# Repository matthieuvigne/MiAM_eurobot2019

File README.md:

# MiAM_eurobot2019
## Electronics and code of MiAM's robot for Eurobot 2019.

This repo contains code and electronics design files related the 2019 Eurobot competition of MiAM,
a French team of former students from MINES ParisTech and Arts et Métiers schools.

For older files related to the 2018 robot setup, see [MiAM_eurobot2018](https://github.com/matthieuvigne/MiAM_eurobot2018) repo.
The 2019 repo started from the 2018, but has adapted to the new robot architecture (motors, sensors...)

See [MiAM website](https://www.miam-robotique.fr/) (in French).

### Contents
 - [**ArduinoFunnyAction**](./ArduinoFunnyAction) and [**ArduinoSlave**](./ArduinoSlave): arduino code for the funny action (experiment) and for the Raspberry pi slave
 of the main robot.
 - [**ConfigRPi**](./ConfigRPi): Inscruction for configuring a raspberry pi to have headless wifi connection and to run our code.
 - [**Electronics**](./Electronics): wiring diagram and PCBs for the main robot.
 - [**RobotCode**](./RobotCode): onboard C++ code, running on Beaglebone Black or Raspberry pi processor.
 - [**miam_py**](./miam_py): a python package for reading and plotting a log file from the robot.
 - [**StrategyViewer**](./StrategyViewer): A GTK+-based viewer for the trajectories for the robots.

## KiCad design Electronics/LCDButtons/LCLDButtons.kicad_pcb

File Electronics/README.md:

# Electronics

This folder contains the general wiring diagram of the robot, along with schematics and PCB files for custom boards,
realised with Kicad.

 - RPiShield: a somewhat generic shield ("hat") for the Raspberry Pi, to make GPIO and serial connections easier. This
 shield exposes, in a well-ordered manner:
	- the I2C port, with several pins to easily wire multiple salves.
	- three SPI ports (SPI0.0, SPI0.1 and SPI1.2), with a buffer protecting the CS line (useful for the L6470 breakout board,
	where this line is driven high at startup, possibly before the Raspberry Pi is powered up).
	- the UART port.
	- both hardware PWM pins.
	- three onboard LEDs.
	- the remaining 8 GPIOs.
 Note that this shield does not include any buffering on GPIOs.

 - library: a folder containing a Kicad library "MiAM", containing random custom parts used in these boards.

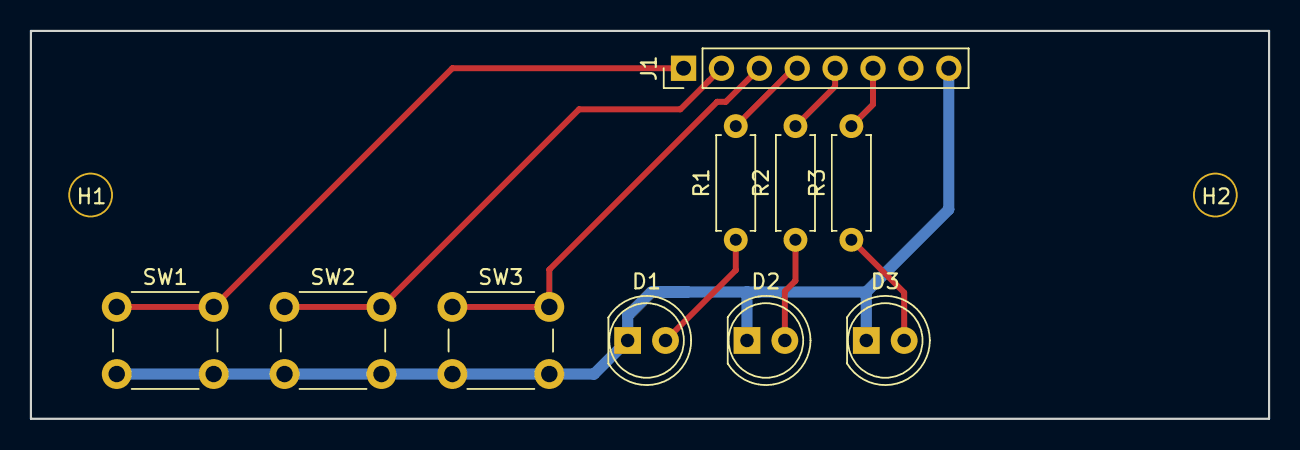
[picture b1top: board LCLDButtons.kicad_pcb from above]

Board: 2 copper layers, 83.0 x 26.0 mm, 12 parts (0 on the bottom side), 10 nets.

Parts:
D1, D2, D3: LED; LED_D5.0mm
H1, H2: Hole_3mm_PTH; NPTH_3mm_ID
J1: Conn_01x08; Pin_Header_Straight_1x08_Pitch2.54mm
R1, R2, R3: 1k; R_Axial_DIN0207_L6.3mm_D2.5mm_P7.62mm_Horizontal
SW1, SW2, SW3: SW_SPST; SW_PUSH_6mm

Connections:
/PB0: J1.4, R1.2
/PC2: J1.3, SW3.1
/PC4: J1.2, SW2.1
/PC7: J1.1, SW1.1
/RX: J1.6, R3.2
/TX: J1.5, R2.2
GND: D1.1, D2.1, D3.1, J1.8, SW1.2, SW2.2, SW3.2
unnamed: D1.2, R1.1
unnamed: D2.2, R2.1
unnamed: D3.2, R3.1

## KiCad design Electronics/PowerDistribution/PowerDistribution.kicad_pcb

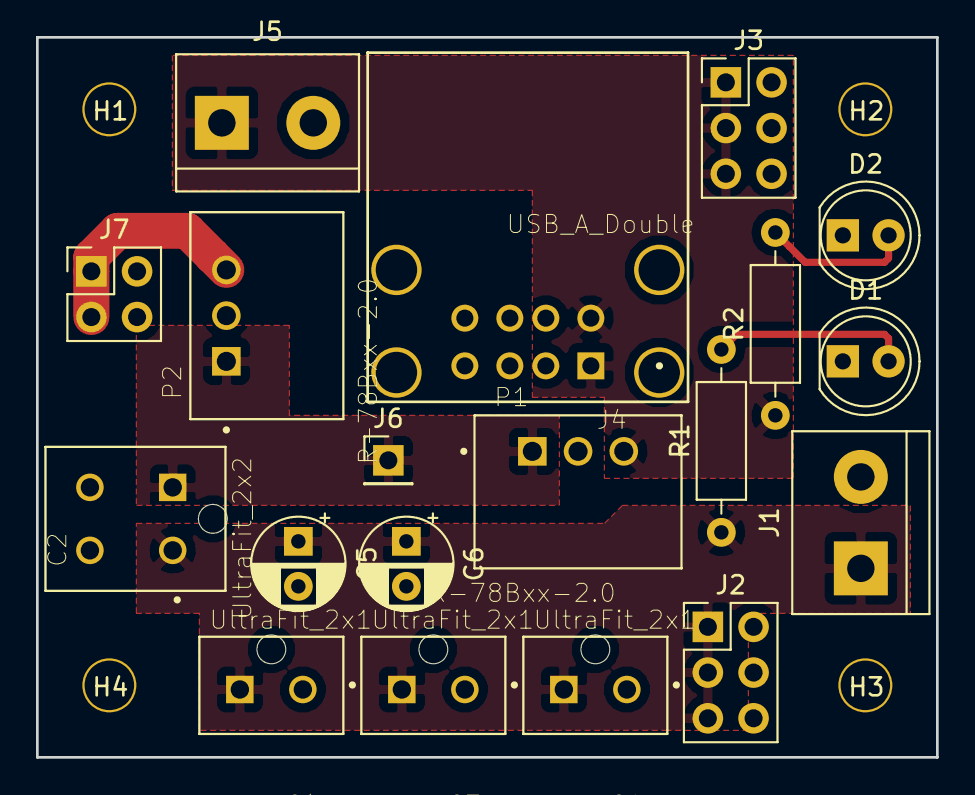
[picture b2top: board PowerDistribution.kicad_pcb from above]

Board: 2 copper layers, 50.0 x 40.0 mm, 23 parts (0 on the bottom side), 7 nets.

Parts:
C1, C3, C4: UltraFit_2x1; MOLEX_1722861102
C2: UltraFit_2x2; MOLEX_1722981104
C5, C6: CP1; CP_Radial_D5.0mm_P2.50mm
D1, D2: LED; LED_D5.0mm
H1, H2, H3, H4: Hole_3mm_PTH; NPTH_3mm_ID
J1, J5: Screw_Terminal_01x02; TerminalBlock_bornier-2_P5.08mm
J2, J3: Conn_02x03_Odd_Even; PinHeader_2x03_P2.54mm_Vertical
J4: USB_A_Double; USB_A_Double_2410_05
J6: Conn_01x01_Male; PinHeader_1x01_P2.54mm_Vertical
J7: Conn_02x02_Odd_Even; PinHeader_2x02_P2.54mm_Vertical
P1, P2: R-78Bxx-2.0; CONV_R-78Bxx-2.0
R1: 2k; R_Axial_DIN0207_L6.3mm_D2.5mm_P10.16mm_Horizontal
R2: 600; R_Axial_DIN0207_L6.3mm_D2.5mm_P10.16mm_Horizontal

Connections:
+12V: C2.1, J6.1, P1.1, P2.1
GND: C1.2, C2.4, C3.2, C4.2, C5.2, C6.2, D1.1, D2.1, J1.2, J2.2, J2.4, J2.6, J3.2, J3.4, J3.6, J4.4, J5.2, J7.2, J7.4, P1.2, P2.2
unnamed: C1.1, C2.2, C3.1, C4.1, C5.1, C6.1, J1.1, J2.1, J2.3, J2.5, R1.1
unnamed: D1.2, R1.2
unnamed: D2.2, R2.2
unnamed: J3.1, J3.3, J3.5, J4.1, J5.1, P1.3, R2.1
unnamed: J7.1, J7.3, P2.3

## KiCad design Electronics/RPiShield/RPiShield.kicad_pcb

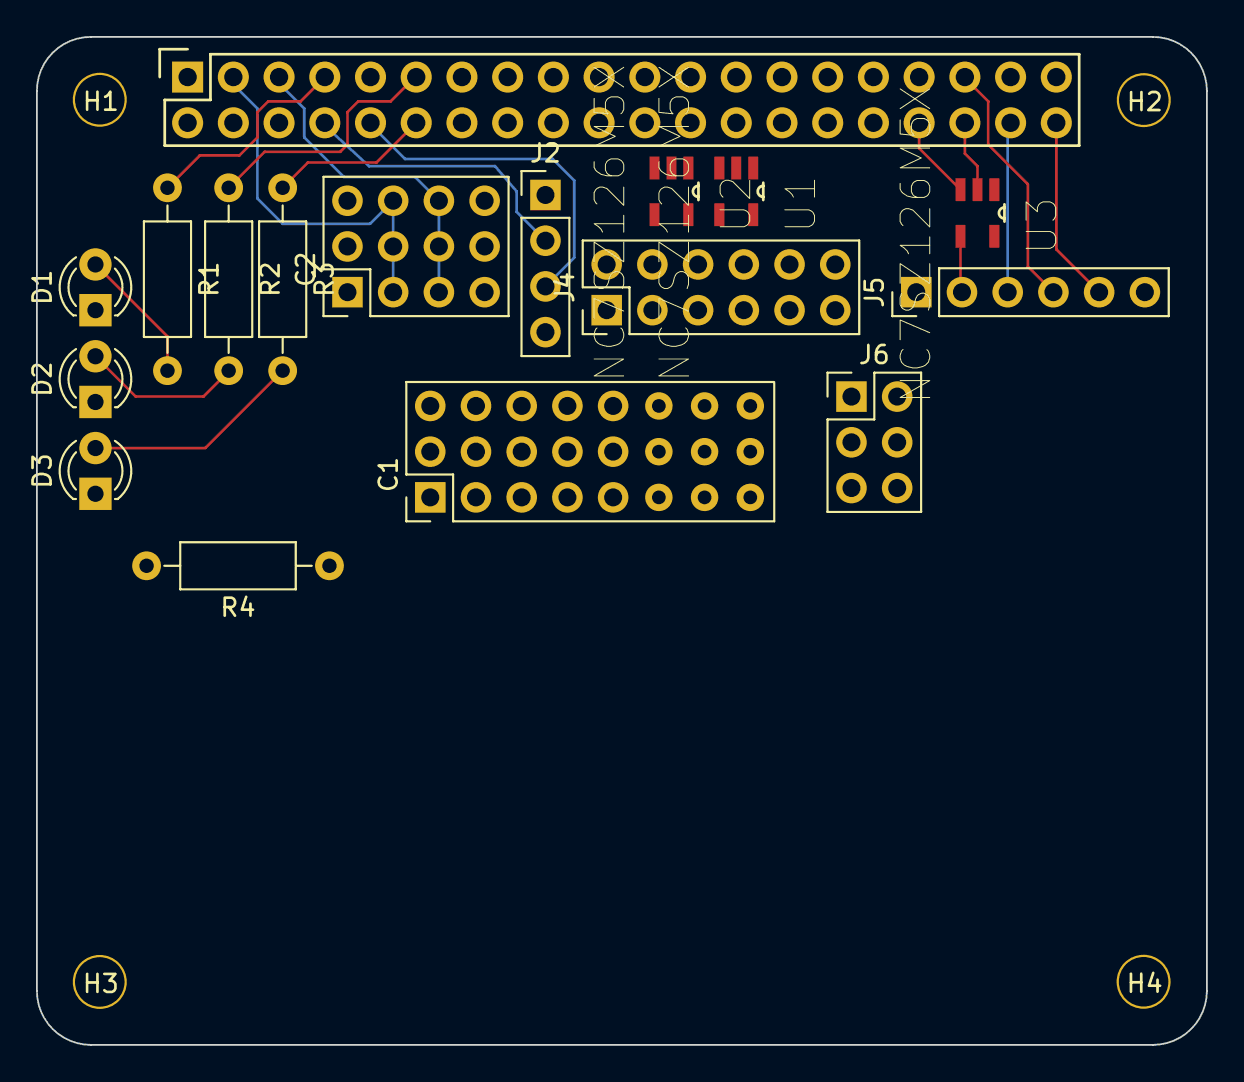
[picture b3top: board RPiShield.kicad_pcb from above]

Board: 2 copper layers, 65.0 x 56.0 mm, 21 parts (0 on the bottom side), 35 nets.

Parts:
C1: Conn_03x08; Pin_Header_Straight_3x08_Pitch2.54mm
C2: Conn_03x04; Pin_Header_Straight_3x04_Pitch2.54mm
D1, D2, D3: LED; LED_D3.0mm
H1, H2, H3, H4: Hole_3mm_PTH; NPTH_3mm_ID
J1: PI40HAT; Socket_Strip_Straight_2x20
J2: Conn_01x04; Pin_Header_Straight_1x04_Pitch2.54mm
J4: Conn_02x06_Odd_Even; Pin_Header_Straight_2x06_Pitch2.54mm
J5: Conn_01x06; Pin_Header_Straight_1x06_Pitch2.54mm
J6: Conn_02x03_Odd_Even; Pin_Header_Straight_2x03_Pitch2.54mm
R1, R2, R3: 220; R_Axial_DIN0207_L6.3mm_D2.5mm_P10.16mm_Horizontal
R4: 20k; R_Axial_DIN0207_L6.3mm_D2.5mm_P10.16mm_Horizontal
U1, U2, U3: NC7SZ126M5X

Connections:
+3V3: C1.2, C1.5, C1.8, C1.11, C1.14, C1.17, C1.20, C1.23, C2.1, C2.2, C2.3, J1.1, J1.17, J2.1, J4.1, J4.2, J5.1, J6.3, J6.4, R4.1, U1.1, U1.5, U2.1, U2.5, U3.1, U3.5
+5V: J1.2, J1.4
/GPIO_5: C1.18, J1.29
/GPIO_6: C1.21, J1.31
/GPIO_12_PWM0: J1.32, J6.1
/GPIO_13_PWM1: J1.33, J6.2
/GPIO_22: C1.6, J1.15
/GPIO_23: C1.9, J1.16
/GPIO_24: C1.12, J1.18
/GPIO_25: C1.15, J1.22
/GPIO_26: C1.24, J1.37
/GPIO_27: C1.3, J1.13
/I2C_SCL: C2.7, C2.8, C2.9, J1.5
/I2C_SDA: C2.4, C2.5, C2.6, J1.3
/SPI0_CLK: J1.23, J4.9, J4.10
/SPI0_MISO: J1.21, J4.7, J4.8
/SPI0_MOSI: J1.19, J4.5, J4.6
/SPI0_SS0: J1.24, U1.2
/SPI0_SS1: J1.26, U2.2
/SPI1_CLK: J1.40, J5.5
/SPI1_MISO: J1.35, J5.4
/SPI1_MOSI: J1.38, J5.3
/SPI1_SS2: J1.36, U3.2
/UART_RX: J1.10, J2.3
/UART_TX: J1.8, J2.2
GND: C1.1, C1.4, C1.7, C1.10, C1.13, C1.16, C1.19, C1.22, C2.10, C2.11, C2.12, D1.1, D2.1, D3.1, J1.6, J1.9, J1.14, J1.20, J1.25, J1.30, J1.34, J1.39, J2.4, J4.11, J4.12, J5.6, J6.5, J6.6, R4.2, U1.3, U2.3, U3.3
unnamed: D1.2, R1.2
unnamed: D2.2, R2.2
unnamed: D3.2, R3.2
unnamed: J1.7, R1.1
unnamed: J1.11, R2.1
unnamed: J1.12, R3.1
unnamed: J4.3, U1.4
unnamed: J4.4, U2.4
unnamed: J5.2, U3.4

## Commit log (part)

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2017-11-21 [ProgrammationBBB] Ajout du dossier ProgrammationBBB
    - Ajout de la bibliothèque BBBEurobot
    - Ajout du programme de test TestADNS (pour démo de l'usage de BBBEurobot et pour un exemple de fichier CMakeLists)
    - Ajout d'un tuto pour la configuration d'un environnement de cross-compilation.
    - Mise à jour du README principal + README dans ProgrammationBBB.
2017-12-09 [ProgrammationBBB] Ajout de la documentation et de l'initialisation.
    - Ajout du dossier doc générant une documentation doxygen de BBBEurobot.
    - Ajout de l'overlay Eurobot-00A0.dts pour activer les ports série.
    - Ajout de BBBGpio - gestion des ports série uniquement.
    - Supression de IRReciever (inutile pour le moment).
    - Mise a jour de TestADNS.
2018-01-25 [BBBEurobot] Add PCAServoDriver, code for the ServoDriver board.
2018-01-29 [BBBEurobot] Add driver for LCD screen. Update documentation.
    Note that the LCD driver is not fully fonctional yet: the screen
    only works with one line activated.
2018-02-23 [BBB-Eurobot] Update IMU driver to work with Pololu MiniIMU-V5 instead of V3.
    Update DTO file - set I2C frequency to 400kHz instead of 100kHz.
    Fix bug in enabling GPIOs.
2018-03-01 [BBB-Eurobot] Update SPI handling.
    - Modify SPI-related struct. to have default frequency at 800kHz instead
    of taking 'speed' as an argument.
    - Modify ADNS9800 api to be more consistent with the rest of the library.
2018-03-03 [programming] Added test script for all sensors.
    Add TestSensors code, that test all components of the robot except motors.
    This code tests:
    - digital input and output (leds)
    - analog input
    - IMU
    - Mouse sensor
2018-03-17 [overlay] Add UART4 to device tree overlay file (for new servo driver).
2018-04-08 [BBB-Eurobot] Fixup of servo driver.
    Maestro servo driver tested and functional.
2018-04-10 [BBB-Eurobot] Modify L6470Driver API.
    - Add setStepMode function.
    - Drive now starts in full step mode.
    - L6470_initMotion no longer takes separate accel and decel values.
2018-04-20 Full rewrite of robot positionning and motion on table.
    The code now has an architecture closer to that of last year, with localisation and
    constrol separated:
    - file Localisation.c implements a thread that runs robot position estimation and logging.
    - file MotionController implements blocking functions for robot motion (rotation, translation,
    goTo).
2018-04-20 [Eurobot Code] Many minor code changes.
    - Robot: replace RobotTarget.parameter by RobotTarget.RobotPosition
    - MotionController: change motor current from 1.5A running (1.8 blocked) to 2.0A - 2.1A.
    - Main: add mouse sensor init.
    - Strategy: uncomment testing trajectory.
2018-04-20 [eurobotCode] Fix code according to March 4th Skype
    - Fix currentTime & lastTime in MotionController.c
    - Replace timerThread with a g_timeout to end the match
2018-04-20 [EurobotCode] Fixup of motion, wait and infrared.
    Test waitForStart and infrared sensors, fixed code bugs.
    Test trapezoid trajectory for rotation, update PID gains.
    Fix error in computeRotationAngle.
2018-04-20 Update init after code testing.
2018-04-30 [EurobotCode] Stategy as of 28th april.
2018-05-05 [BBB-Eurobot] Raise default L6470 stall and OCD thersholds.
2018-05-06 [EurobotCode] Remove logging of unused gyroX and gyroY, add logging of Kalman bias.
2018-05-09 [BBB-Eurobot] Ignore stall errors.
2018-05-10 [EurobotCode] Modify infrared threshold and mechanism.
    Make IR more robust - ignore it for the first second.
2018-06-27 Update all READMEs, translate them all to English.
    Change folder name to English, translate wiring diagram, translate all
    README files.
2018-06-27 [BBB-Eurobot] Add Metronome code for precise time handling.
    - Add Metronome struct and functions to enable more precise periodic code execution
    than using standard sleep or g_timeout.
    - Use Metronome in Localisation, where we want to run localisation routine every 10ms.
    The new implementation is much more precise, and does not drift as much (total drift < 0.1%
    against 5% ; note that due to CPU load, the time between two iterations still varies, but
    not as much as before).
2018-07-08 [BBBEurobot] Add debug/release build option.
    Code can now be built in debug or release. In release mode, -O3 flag
    is used and errors that print data to the console ouptut are silent.
2018-07-08 [BBBEurobot] Create new logger struct.
    Create functions for logging easily data to a CSV log file.
2018-08-14 Full code rework to work with Raspberry Pi.
    - Rename Code_BBB to RobotCode.
    - Rework BBBEurobot library to be more generic in order to work with the Raspberry Pi as well.
    New library, MiAMEurobot, works for both processors. Different includes are used to declare the serial ports
    of each board, but the rest is common.
    - Add code for an arduino to read a serial encoder and send it through UART.
    - Add test code for new drive train: this code servos a stepper motor onto an encoder through an arduino.
2018-08-17 [MiAMEurobot] Add GPIO access functions for Raspberry Pi.
    GPIO access is done using mmap, enabling very fast (2.9MHz) access to all GPIOs.
2018-09-17 [MiAMEurobot] V1.1: add driver for two L6470, daisy chained.
    - Add code for driving two L6470 daisy chained on the same SPI port,
    as is the case for ST X-NUCLEO-IHM02A1 board.
    - Cleanup SPI-Wrapper from dead code, added modification to work on
    Raspberry Pi (not tested on Beaglebone, but should work as well).
    - Increase default SPI clock for L6470 to 4MHz.
2018-10-13 [MiAMEurobot] Update trajectory and add PID class.
    - Remove isTrajectoryDone from trajectory point, this can be deduced by getDuration.
    - Add PID class implementation.
2018-10-13 [miam_py] Add script to analyse robot motion on the table.
2018-11-01 [MiAMEurobot/trajectory] Add arc to trajectory generation.
    - Add a circular trajectory to the trajectory list.
    - Add a function to create a trajectory with rounded corners through a set of points.
    - Make RobotPosition a real class, and implement basic operations on it.
2018-12-03 [Electronics] PCB - first complete version.
2019-01-05 [MiAMEurobot] Remove dependency in glib
    Remove code dependency in glib by rewriting the code to rely on C++ standard library instead.
    Update some files from using C struct to C++ classes - this wasn't done everywhere.
2019-01-19 [MPC/PathPlanner] Add a function to compute a feasible path from a list of waypoints
    * Use RobotPosition, TrajectoryPoint from miam
    * Use ACADO to compute a feasible trajectory
    * Return a TrajectoryVector
2019-01-20 [MPC/PathPlanner] Fix issue in the definition of N: nb of intervals vs N+1: nb of points
2019-02-07 [MPC/CodeGeneration] Add a real-time MPC custom solver
    * Use ACADO code generation tool to make a custom solver for the main robot
    * Make a function that gives the next state to reach according to a reference trajectory and a perturbated state
    * Update the current pathplanning function to allow for custom start and end states
2019-02-16 [MiAMEurobot][DrivetrainTest] Update library and add composent tests.
    - MiAMEurobot: many minor improvements and C++ code update. Added missing files.
    - Create unit tests for testing individual components, mostly made for the wiring.
2019-02-21 [MiAMEurobot] Add function for computing kinematics ; change convention to direct frame
    - Add DrivetrainKinematics for computing the kinematics of the drivetrain in a unified manner.
    - Switch back to using a standard direct frame (y upward and no longer downward). This is still work
    in progress, some old convention may still be present.
2019-02-21 [MainRobotCode] Remove glib dependency.
2019-02-23 [MiAMEurobt / MainRobotCode] Fixup after real robot testing
    - [MiAMEurobot] Fix bug in kinematics
    - [MainRobotCode] Add partial servo configuration after testing.
    - [MainRobotCode] Robot dimension parameter tunning.
2019-02-24 [PathPlanner] Add tests for SampleTrajectory IOs
2019-02-24 [PathPlanner] Fix issue in conversion to SampledTrajectory
2019-02-24 [PathPlanner] Fix issue in which one could not solve more than 1 OCP
    * ACADO uses static counters for diff states, controls and params
    These counters have to be reset before each OCP
    * Add a zigzag curve example
2019-02-24 [PathPlanner][MiAMEurobot/io] Switch indents from tabs to spaces.
2019-02-25 [PathPlanner] Add zigzag trajectories
2019-02-27 [MainRobotCode] Fix instant speed getter
    * Fix previous unfinished commit
    * Switch to BaseSpeed
2019-03-17 [MiAMEurobot] Internal bug fixup<
    - Fix bug in L6470 driver where any value read from the boards corresponded to the first controller only.
    - Raspberry pi GIOP: fix bug in gpio output causing all outputs to toggle together.
2019-03-22 [MainRobotCode] Add init function.
    Add function to properly initialize the robot in Robot class.
2019-03-25 [MiAMEurobot] Beaglebone: add PWM support.
    - Add cape to enable EHRPWM2A and EHRPWM2B ports.
    - Add function to set PWM signal, and a custom function to generate RC-style servo commands.
2019-03-26 [MiAMEurobot] Update L6470 driver to support external crystal clock.
    This improves tracking accuracy significatively, as the internal oscillator
    is wrong by about 5%.
2019-03-28 [RobotCode] Update beaglebone support ; beginning of code for Secondary robot.
    - Change the way overlays are loaded because the previous overlay no longer
    works after kernel update ; for now, use separate off-the-shelf overlays.
    - Add init code with communication to both stepper motors and IMU ; tested.
2019-04-03 [MainRobotCode] Parameter tunning and some debug.
2019-04-03 [MainRobotCode/MPC][PathPlanner] Fix ocp & add PathPlanner init by traj
    * OCP was not defined properly (lacked one constraint)
    * Fix N in PP OCP for consistency (number of intervals)
    * Now PP can be initialized with a Trajectory
2019-04-03 [MainRobotCode/MPC] Fix MPC and implement static class MPCsolver
    * Readapt cost weighting in the solver generation code. MPC now
    prioritizes the error on the trajectory correctly.
    * Create a static class MPCsolver to handle the solver's intitialization
    (both solver variables and new trajectory).
    * Thus Trjajectory does not have to be modified anymore and Robot does
    not have to handle the initialization by itself.
2019-04-03 [MainRobotCode] Fix CMakeList.txt
2019-04-12 [MiAMEurobot] Fix errors when computing circle trajectories.
    This is a remanant of the sign change on the Y axis that wasn't replicated everywhere.
2019-04-21 [RobotCode, SecondaryRobot] Prepare code for Eurobot.
    - Create strategy thread ; low-level is now run in main thread.
    - Add heartbeat.
    - Add function to handle IR detection (work in progress).
2019-04-22 [MiAMEurobot] Add AbstractRobot class.
    - Add abstract class representing a robot, for doing basic operations
    and sharing a common architecture between both projects.
    - Rework both robot code to comply with AbstractRobot class.
2019-04-22 Add StrategyViewer, a GTK-based viewer for displaying robot trajectories.
    This is meant to be used for strategy design.
2019-04-27 Fix bug in LCD driver. Various improvements to secondary robot code.
2019-04-27 [MiAMEurobot] BBBGpio: add try/catch to prevent segfault.
    Secondary robot code: fix purple side miror. Use PID for correcting open-loop
    velocity trajectory based on motor position.
2019-04-28 [miam_py] Add support for regular expressions in plot.
2019-05-01 [MiAMEurobot] Fix ArcCircle trajectory angle being discontinuous for some motions.
2019-05-02 [MainRobotCode/MPC] Add a velocity controlled solver
2019-05-11 Strategy Viewer: update viewer, add an obstacle to test trajectory generation.
2019-05-11 [Trajectory] Add TrajectoryVector class.
2019-05-11 [MiamEurobot] Update LCDScreen to work asyncronously.
    - LCDScreen now works in a background thread, preventing client code jamming.
    - Secondary robot: display continuously IR data.
2019-05-17 [Main Robot Code] Add code for handling experiment.
2019-05-22 [MainRobotCode/Rail] Add low level P control to the rail
    * Rail control now occurs in the low level thread
    * A P controller is used to find the right control
2019-05-25 Main Robot: update code: working strategy with no avoidance.
2019-05-25 [Detection] Working detection code - no avoidance present yet.
2019-05-26 [MainRobot] Update strategy (not tested on table yet).
    - MiAMEurobot: fix typo in trajectory/Utilities.h
    - MainRobot: update code to include handling of last atoms.
    - Strategy viewer: update code to reflect new strategy and to be closer to the robot code.
2019-05-29 [MainRobot] Improve bluetooth initialization.
2019-05-29 Robot: further tuning.
2019-05-30 Detection: detect using a rectangle rather than a circle.
    Second match code.
2019-05-31 Main robot: update detection state machine. Improve strategy. Code of Match 3.
